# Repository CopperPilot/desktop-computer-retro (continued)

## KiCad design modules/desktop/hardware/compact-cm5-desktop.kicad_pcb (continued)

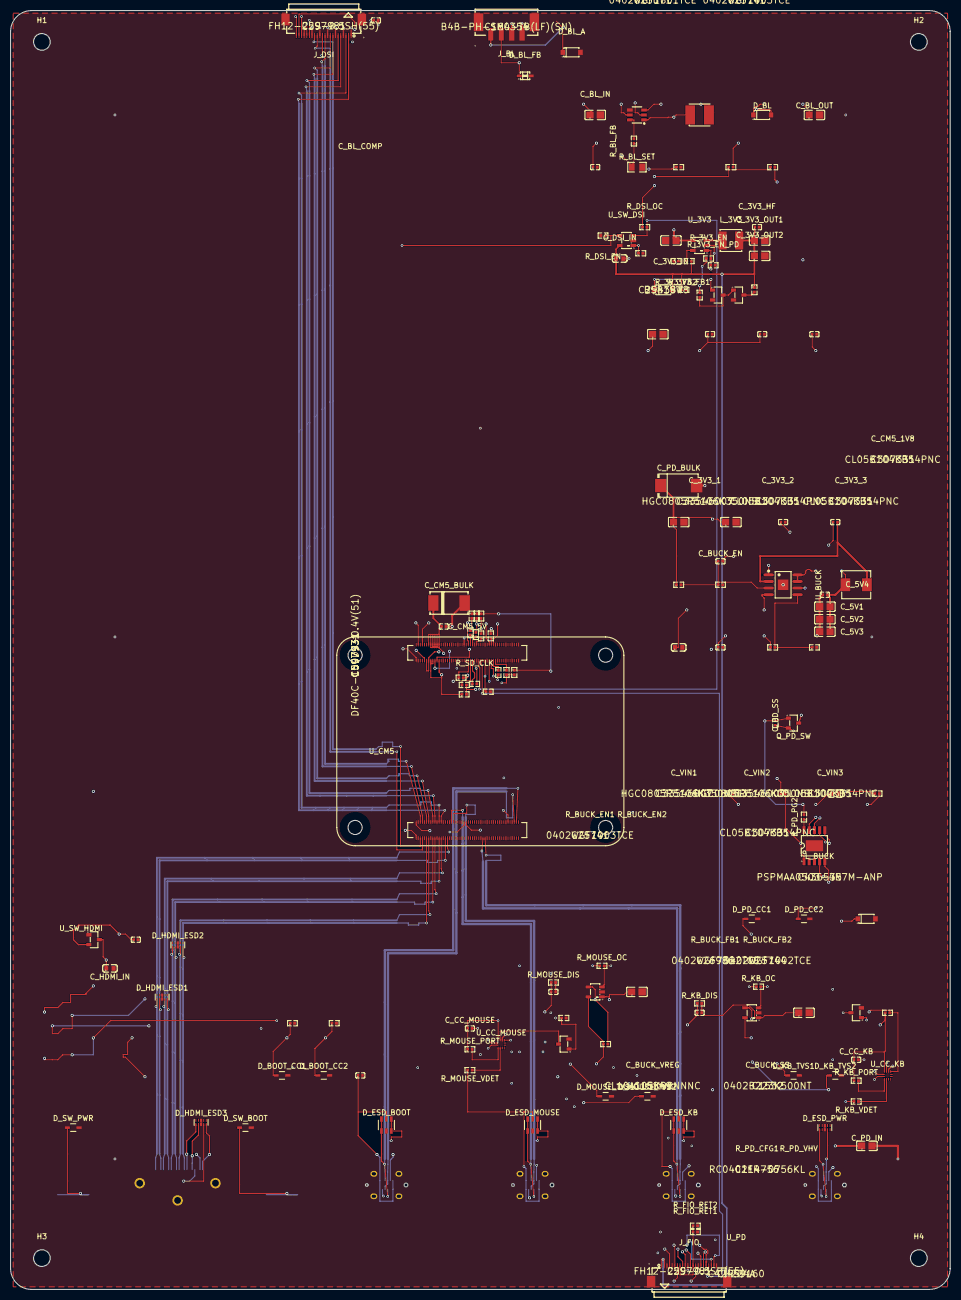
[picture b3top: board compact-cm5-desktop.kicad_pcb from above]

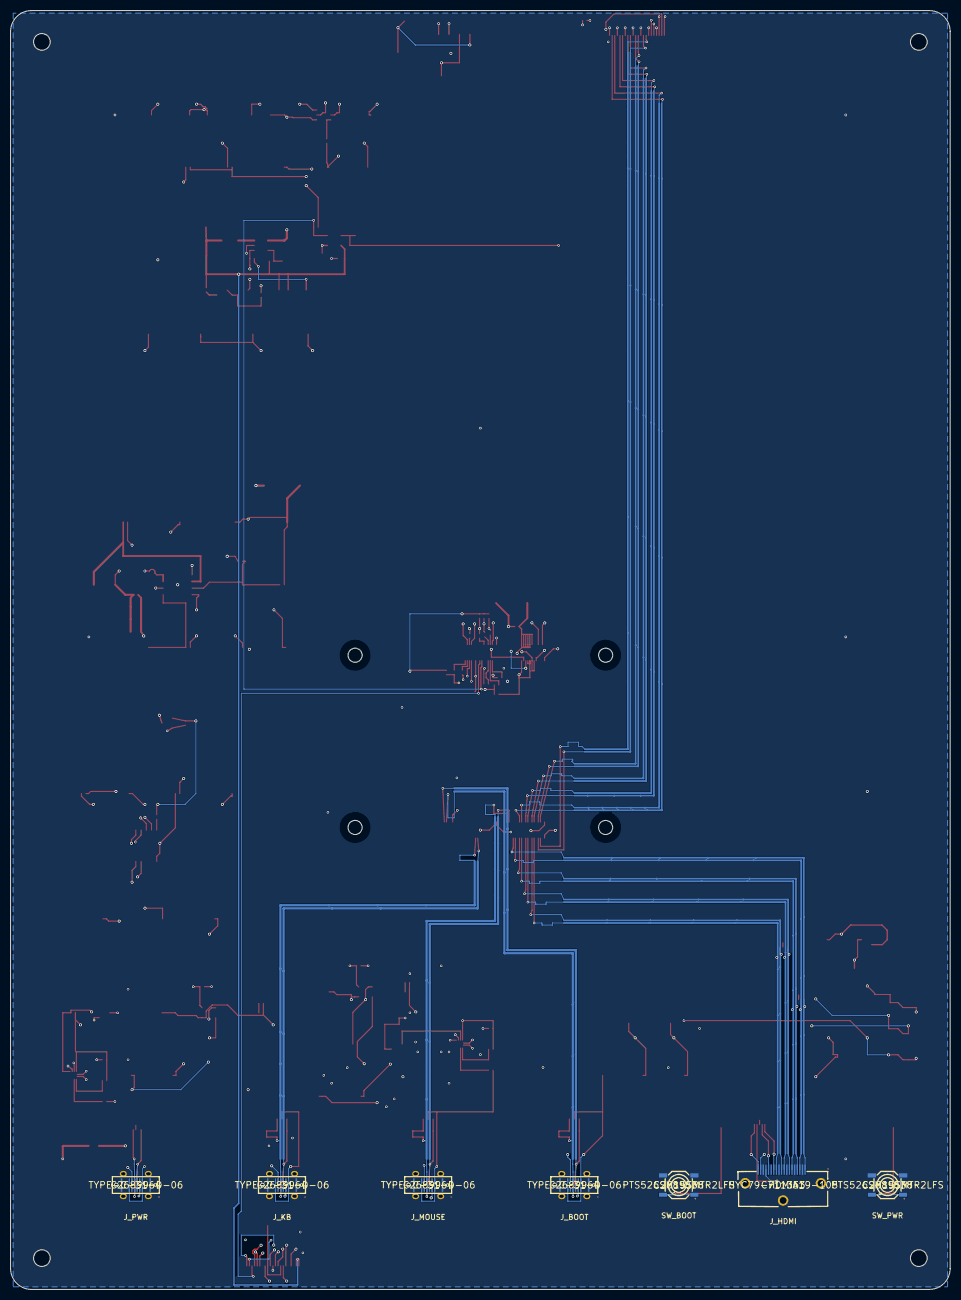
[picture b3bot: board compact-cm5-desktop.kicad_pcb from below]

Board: 4 copper layers, 180.0 x 245.0 mm, 147 parts (7 on the bottom side), 112 nets.

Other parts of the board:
H1, H2, H3, H4: MountingHole_3.2mm_M3

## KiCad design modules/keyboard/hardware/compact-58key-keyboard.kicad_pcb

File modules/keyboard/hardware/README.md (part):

# KiCad project — Compact 58-Key Mechanical Desktop Keyboard

Generated from `rea/spec.yaml` by rea-hardware (fab rules, stackup, outline at the origin, mounting
holes), then completed by the electrical agent. Every placed part carries an `LCSC` field and matches
the 150-component `rea/spec.yaml` BOM 1-for-1.

## Architecture & Programming / Bootloader Path

- **MCU & Clocking (`U1`, RP2040, LCSC `C2040`)**:
  - Powered by `3V3_KB` (`IOVDD`, `USB_VDD`, `ADC_AVDD`, `VREG_IN`) with the internal core regulator generating `+1V1` on `VREG_VOUT` (Pin 45) for `DVDD` (Pins 23, 50).
  - Clocked by a 12.000 MHz SMD3225-4P crystal (`Y1`, Abracon `ABM8-272-T3`, LCSC `C20625731`, rated `C_L = 10 pF`, `ESR <= 50 Ohm` max per RP2040 XOSC specification) matched to 12 pF load capacitors (`C15`, `C16`, LCSC `C1547`, giving `C_load = (12 pF * 12 pF) / 24 pF + 4 pF stray = 10 pF`) and a 1 kOhm damping resistor (`R5`, LCSC `C11702`) on `XOUT`.
  - **Crystal Placement & Layout (`Y1`, `R5`, `C15`, `C16`)**: Placed immediately south of `U1` Pins 20 (`XIN`) and 21 (`XOUT`) at `(186.60, 22.65)` mm (`C15` at `(184.10, 22.65)`, `R5` at `(189.30, 21.65)`, `C16` at `(189.30, 23.35)`). `/XIN`, `/XOUT_MCU`, and `/XOUT_XTAL` are routed 100% on `F.Cu` with zero vias over a continuous, unbroken `B.Cu` ground plane (`/COL9` and `/COL10` are routed outside the crystal boundary at `x <= 183.87 mm`).
- **QSPI Flash, UF2 USB Bootloader & Reset Path (`U2`, `R7`, `SW59`, `R6`, `R8`, `J1`)**:
  - External 16 MB QSPI NOR flash `U2` (`W25Q128JVSIQ`, LCSC `C97521`) connects to `U1` `QSPI_SS`, `QSPI_SCLK`, and `QSPI_SD0..SD3`.
  - A 10 kOhm 1% pull-up resistor `R7` (`0402WGF1002TCE`, LCSC `C25744`) placed adjacent to `U2.1` (`~{CS}`) pulls `QSPI_SS_N` up to `3V3_KB` so that flash `~{CS}` tracks `3V3_KB` during power-up and reset while `U1.56` is tri-stated.
  - Bottom-mounted tactile switch `SW59` (`TS-1187A-B-A-B`, LCSC `C318884`, aligned with the bottom enclosure aperture `F_BOOTSEL` and captive actuator `A_BOOTSEL`) pulls `QSPI_SS_N` to `GND` through a 1 kOhm isolation resistor (`R6`, LCSC `C11702`). When `SW59` is pressed, the `R6` / `R7` divider pulls `QSPI_SS_N` to `3.3 V * (1 kOhm / 11 kOhm) = 0.30 V` (`< 0.8 V` `V_IL,max` of `U1` and `U2`).
  - `U1.26` (`RUN`) is pulled up to `3V3_KB` via 10 kOhm 1% resistor `R8` (`0402WGF1002TCE`, LCSC `C25744` at `(196.30, 19.00)` mm).
  - **Reachable post-assembly flashing sequence**: Holding `SW59` via the underside `BOOTSEL` button while plugging the USB-C cable into rear receptacle `J1` (`P_KB_DEV`) powers `VBUS_RAW` -> `F1` (`5V_USB_KB`) -> `U3` (`3V3_KB`) -> `U1` (`VREG_VOUT` = `+1V1`), starts the 12 MHz crystal oscillator (`Y1`), and samples `QSPI_SS_N` low (`0.30 V`) at power-on reset. The RP2040 ROM bootloader then enumerates directly over the wired USB 2.0 D+/D- path (`J1` -> `U4` ESD protection -> `R3`/`R4` 27 Ohm series terminations -> `U1` Pins 46/47) as a USB Mass Storage UF2 programming device without requiring enclosure disassembly.

## Component Rating, Power Tree, ESD Protection & Thermal Verification

- **Coordinated Overcurrent & ESD Protection (`J1`, `C17`, `U4`, `F1`, `D60`, `R1`, `R2`)**:
  - `J1` (`TYPE-C-31-M-12`, LCSC `C165948`): dual `VBUS` contacts (`A4B9`, `B4A9` on `VBUS_RAW`) and dual `GND` contacts (`A1B12`, `B1A12`) plus 4 TH shield tabs rated **5.0 A** total (>= 1.25 A per power contact), exceeding the 0.5 A rail limit and ~65 mA active keyboard current with > 10x margin.
  - **High-Frequency Connector-Side ESD Decoupling & Data-Line Clamping (`C17`, `U4`)**:
    - Local 100 nF 16 V X7R high-frequency ESD decoupling capacitor `C17` (`CL05B104KO5NNNC`, LCSC `C1525` at `(156.40, 8.40)` mm) connects directly between `/VBUS_RAW` and `GND` at `J1` ahead of `F1`.
    - `U4` (`USBLC6-2SC6`, LCSC `C2827654`) is placed immediately adjacent to `J1` at `(159.50, 8.40)` mm (`<= 3 mm` from `J1` pads on `F.Cu` with in-line flow-through routing on `/USB_CONN_DP` and `/USB_CONN_DM`), with Pin 5 (`VBUS`) referenced to `/5V_USB_KB` downstream of `F1` so sustained overvoltage or reverse-polarity faults are current-limited by `F1`.
  - **Series PTC Fuse Isolation & Fuse-Coordinated Shunt TVS Clamping on `5V_USB_KB` (`F1`, `D60`, `C1`)**:
    - `F1` (`BSMD0805-050-24V`, LCSC `C910822`, 0805 PTC resettable fuse at `(158.50, 11.80)` mm): connected in series between `/VBUS_RAW` and `/5V_USB_KB`, rated **24 V**, **500 mA** hold current, **1.0 A** trip current, and **40 A** maximum fault current ($R_{\text{min}} = 0.15\,\Omega$, $R_{\text{typ}} = 0.35\,\Omega$, $R_{1\text{max}} = 0.85\,\Omega$).
    - Immediately downstream of `F1.2` on `/5V_USB_KB` sits a 400 W, 43.6 A peak-pulse, low-clamping 5.0 V unidirectional TVS diode `D60` (`PTVS5V0S1UR-FS`, LCSC `C5380694`, SOD-123FL at `(158.50, 13.90)` mm, $V_{\text{RWM}} = 5.0\text{ V}$, $V_{\text{BR}} = 6.4\text{--}7.0\text{ V}$, $V_{\text{CL}} \le 9.2\text{ V}$ at $I_{\text{PP}} = 43.6\text{ A}$) alongside `U4.5` and 2.2 uF 25 V X7R input decoupling capacitor `C1` (`CL21B225KAFNNNE`, LCSC `C19110` at `(161.30, 12.60)` mm), providing fuse-coordinated overvoltage, reverse-polarity, and ESD clamping ahead of 20 V abs-max LDO `U3`.
  - USB-C UFP (sink) configuration: `CC1` (`J1.A5`) and `CC2` (`J1.B5`) each have dedicated 5.1 kOhm 1% pull-down resistors (`R1` at `(161.50, 3.30)` mm and `R2` at `(153.25, 8.50)` mm, `0402WGF5101TCE`, LCSC `C25905`) connected directly to `GND` on `F.Cu` with zero vias and zero stubs.
- **LDO Voltage Rating, Headroom, Monotonic Placement & Thermal Margin (`U3`, `C1`, `C2`, `C3`, `C4`)**:
  - `U3` (`LDL1117S33R`, STMicroelectronics, LCSC `C435835`, SOT-223-4 at `(166.95, 12.30)` mm in the monotonic power-entry path between `J1`/`F1` and `U2`/`U1`): 3.3 V fixed low-dropout regulator rated **18 V** maximum operating input / **20 V** absolute maximum input (`> 2x` worst-case TVS clamping voltage), **1.2 A** output current capability, low quiescent current **`I_Q = 250 uA` typical / `500 uA` max** (`<< 2.5 mA` USB 2.0 suspend limit), and low dropout **`V_DO = 350 mV` typ / `600 mV` max at 1.2 A** (`< 150 mV` at 250 mA).
  - **Worst-Case Dropout Margin (`> 680 mV` headroom)**: At minimum USB 2.0 bus voltage `VBUS_RAW = 4.40 V`, `I_load = 0.25 A`, and post-trip `R_F1,1max = 0.85 Ohm`, `V_IN,min(U3) = 4.40 V - 0.25 A * 0.85 Ohm = 4.188 V >> 3.35 V + 0.15 V = 3.50 V`.
  - **SOT-223-4 Thermal Margin at Full 0.25 A Continuous Specification**: In SOT-223-4 ($R_{\theta\text{JA}} \approx 60^\circ\text{C/W}$), delivering the full `0.25 A` continuous `3V3_KB` specification in `prompt.md` at `V_IN = 5.0 V` dissipates $P_D = (5.0\text{ V} - 3.3\text{ V}) \times 0.25\text{ A} = 0.425\text{ W}$, producing a junction temperature rise of only $\Delta T_J \approx 25.5^\circ\text{C}$ ($T_J \approx 60.5^\circ\text{C} \ll 125^\circ\text{C}$ max at $35^\circ\text{C}$ enclosure ambient).
  - **Zero-Via Core Regulator & IOVDD Decoupling (`C3`, `C4`)**: `C3` (`1 uF` 25 V X5R, LCSC `C52923` at `(188.35, 10.20)` mm) connects directly on `F.Cu` (`w = 0.20-0.30 mm`, length `1.8 mm`, **zero vias**) to `U1` Pin 45 (`VREG_VOUT`, `/+1V1`), and `C4` (`1 uF` 25 V X5R, LCSC `C52923` at `(190.30, 12.30)` mm) connects directly on `F.Cu` (**zero vias**) to `U1` Pins 42, 43, and 44 (`VREG_IN`, `/3V3_KB`).
- **Capacitor Voltage Ratings (>= 1.5x maximum rail voltage) & USB 2.0 Hot-Plug Inrush Compliance**:
  - `VBUS_RAW` / `5V_USB_KB` rails (5.0 V nominal, 5.25 V max; 1.5x requirement = 7.88 V): `C1` (2.2 uF, **25 V**), `C17` (100 nF, **16 V**). Direct unswitched capacitance on `VBUS` is `2.3 uF <= 10 uF` (`11.5 uC <= 50 uC` USB 2.0 hot-plug limit).
  - `3V3_KB` rail (3.3 V nominal; 1.5x requirement = 4.95 V): `C2` (4.7 uF, **25 V**), `C4` (1 uF, **25 V**), `C7..C14` (8x 100 nF, **16 V**).
  - `+1V1` core rail (1.1 V nominal; 1.5x requirement = 1.65 V): `C3` (1 uF, **25 V**), `C5..C6` (2x 100 nF, **16 V**).
  - `12 MHz Crystal` load network (`XIN` / `XOUT_XTAL`, <= 3.3 V): `C15`, `C16` (12 pF C0G, **50 V**).
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
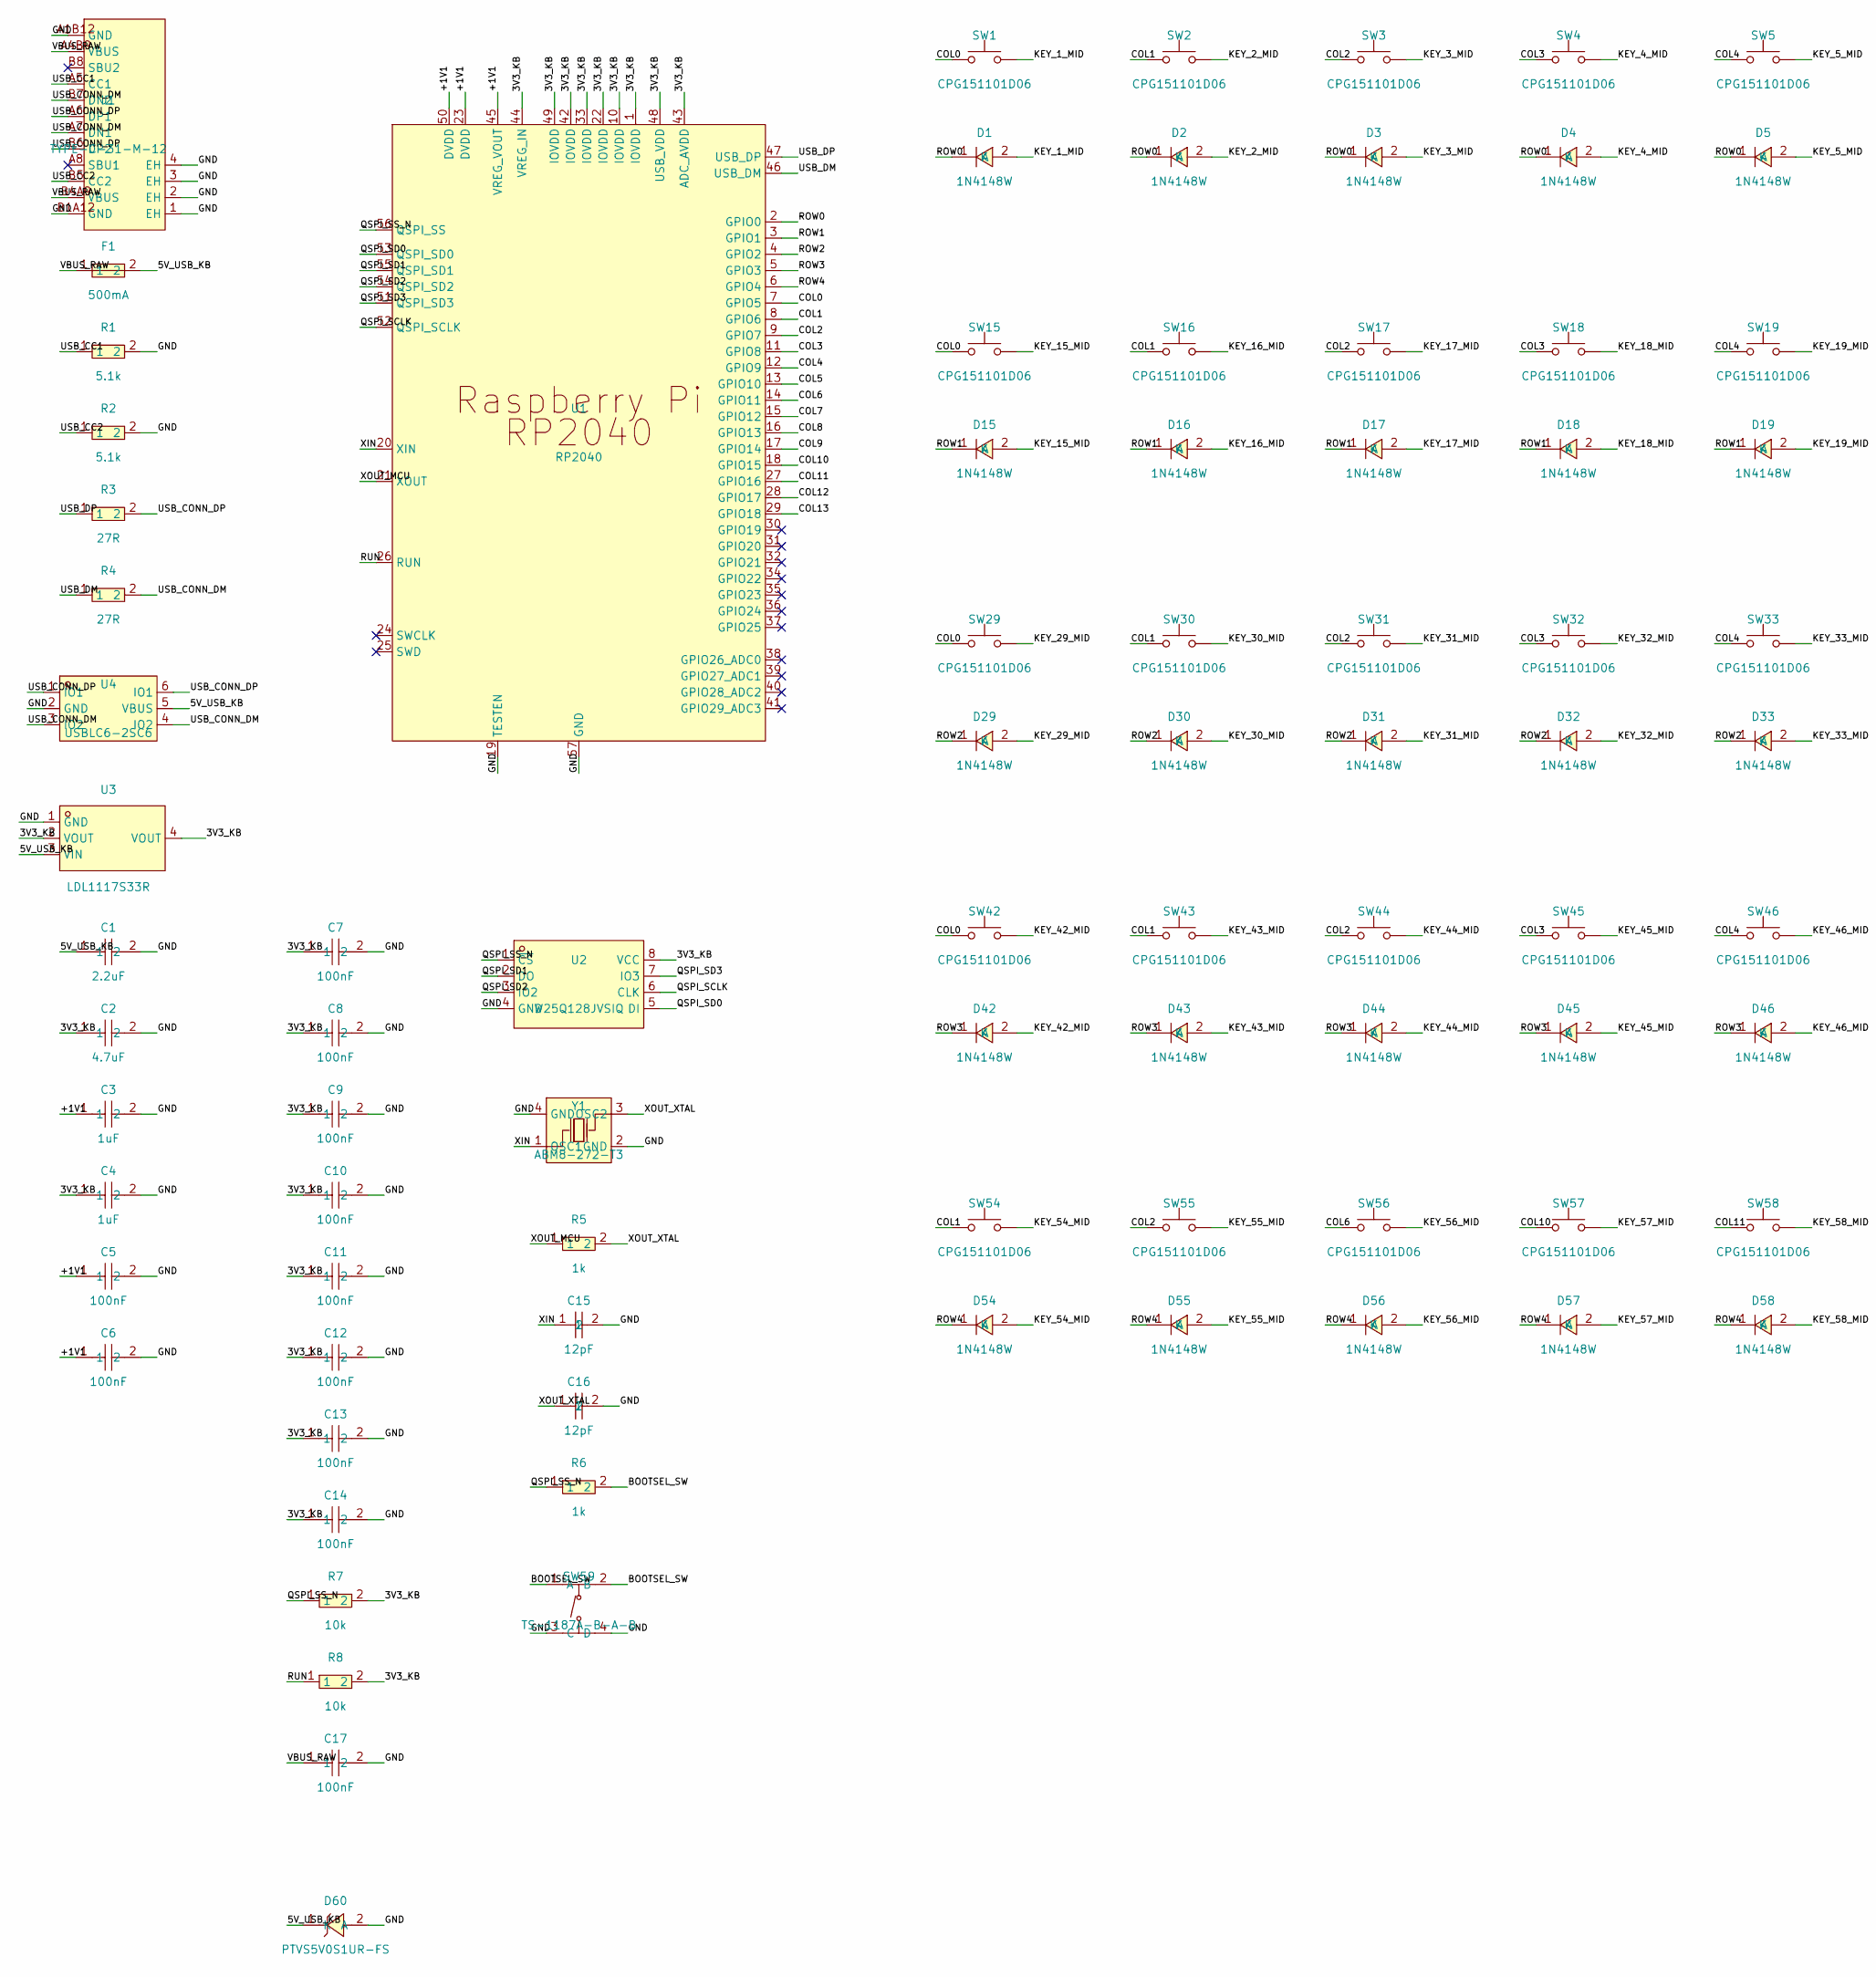
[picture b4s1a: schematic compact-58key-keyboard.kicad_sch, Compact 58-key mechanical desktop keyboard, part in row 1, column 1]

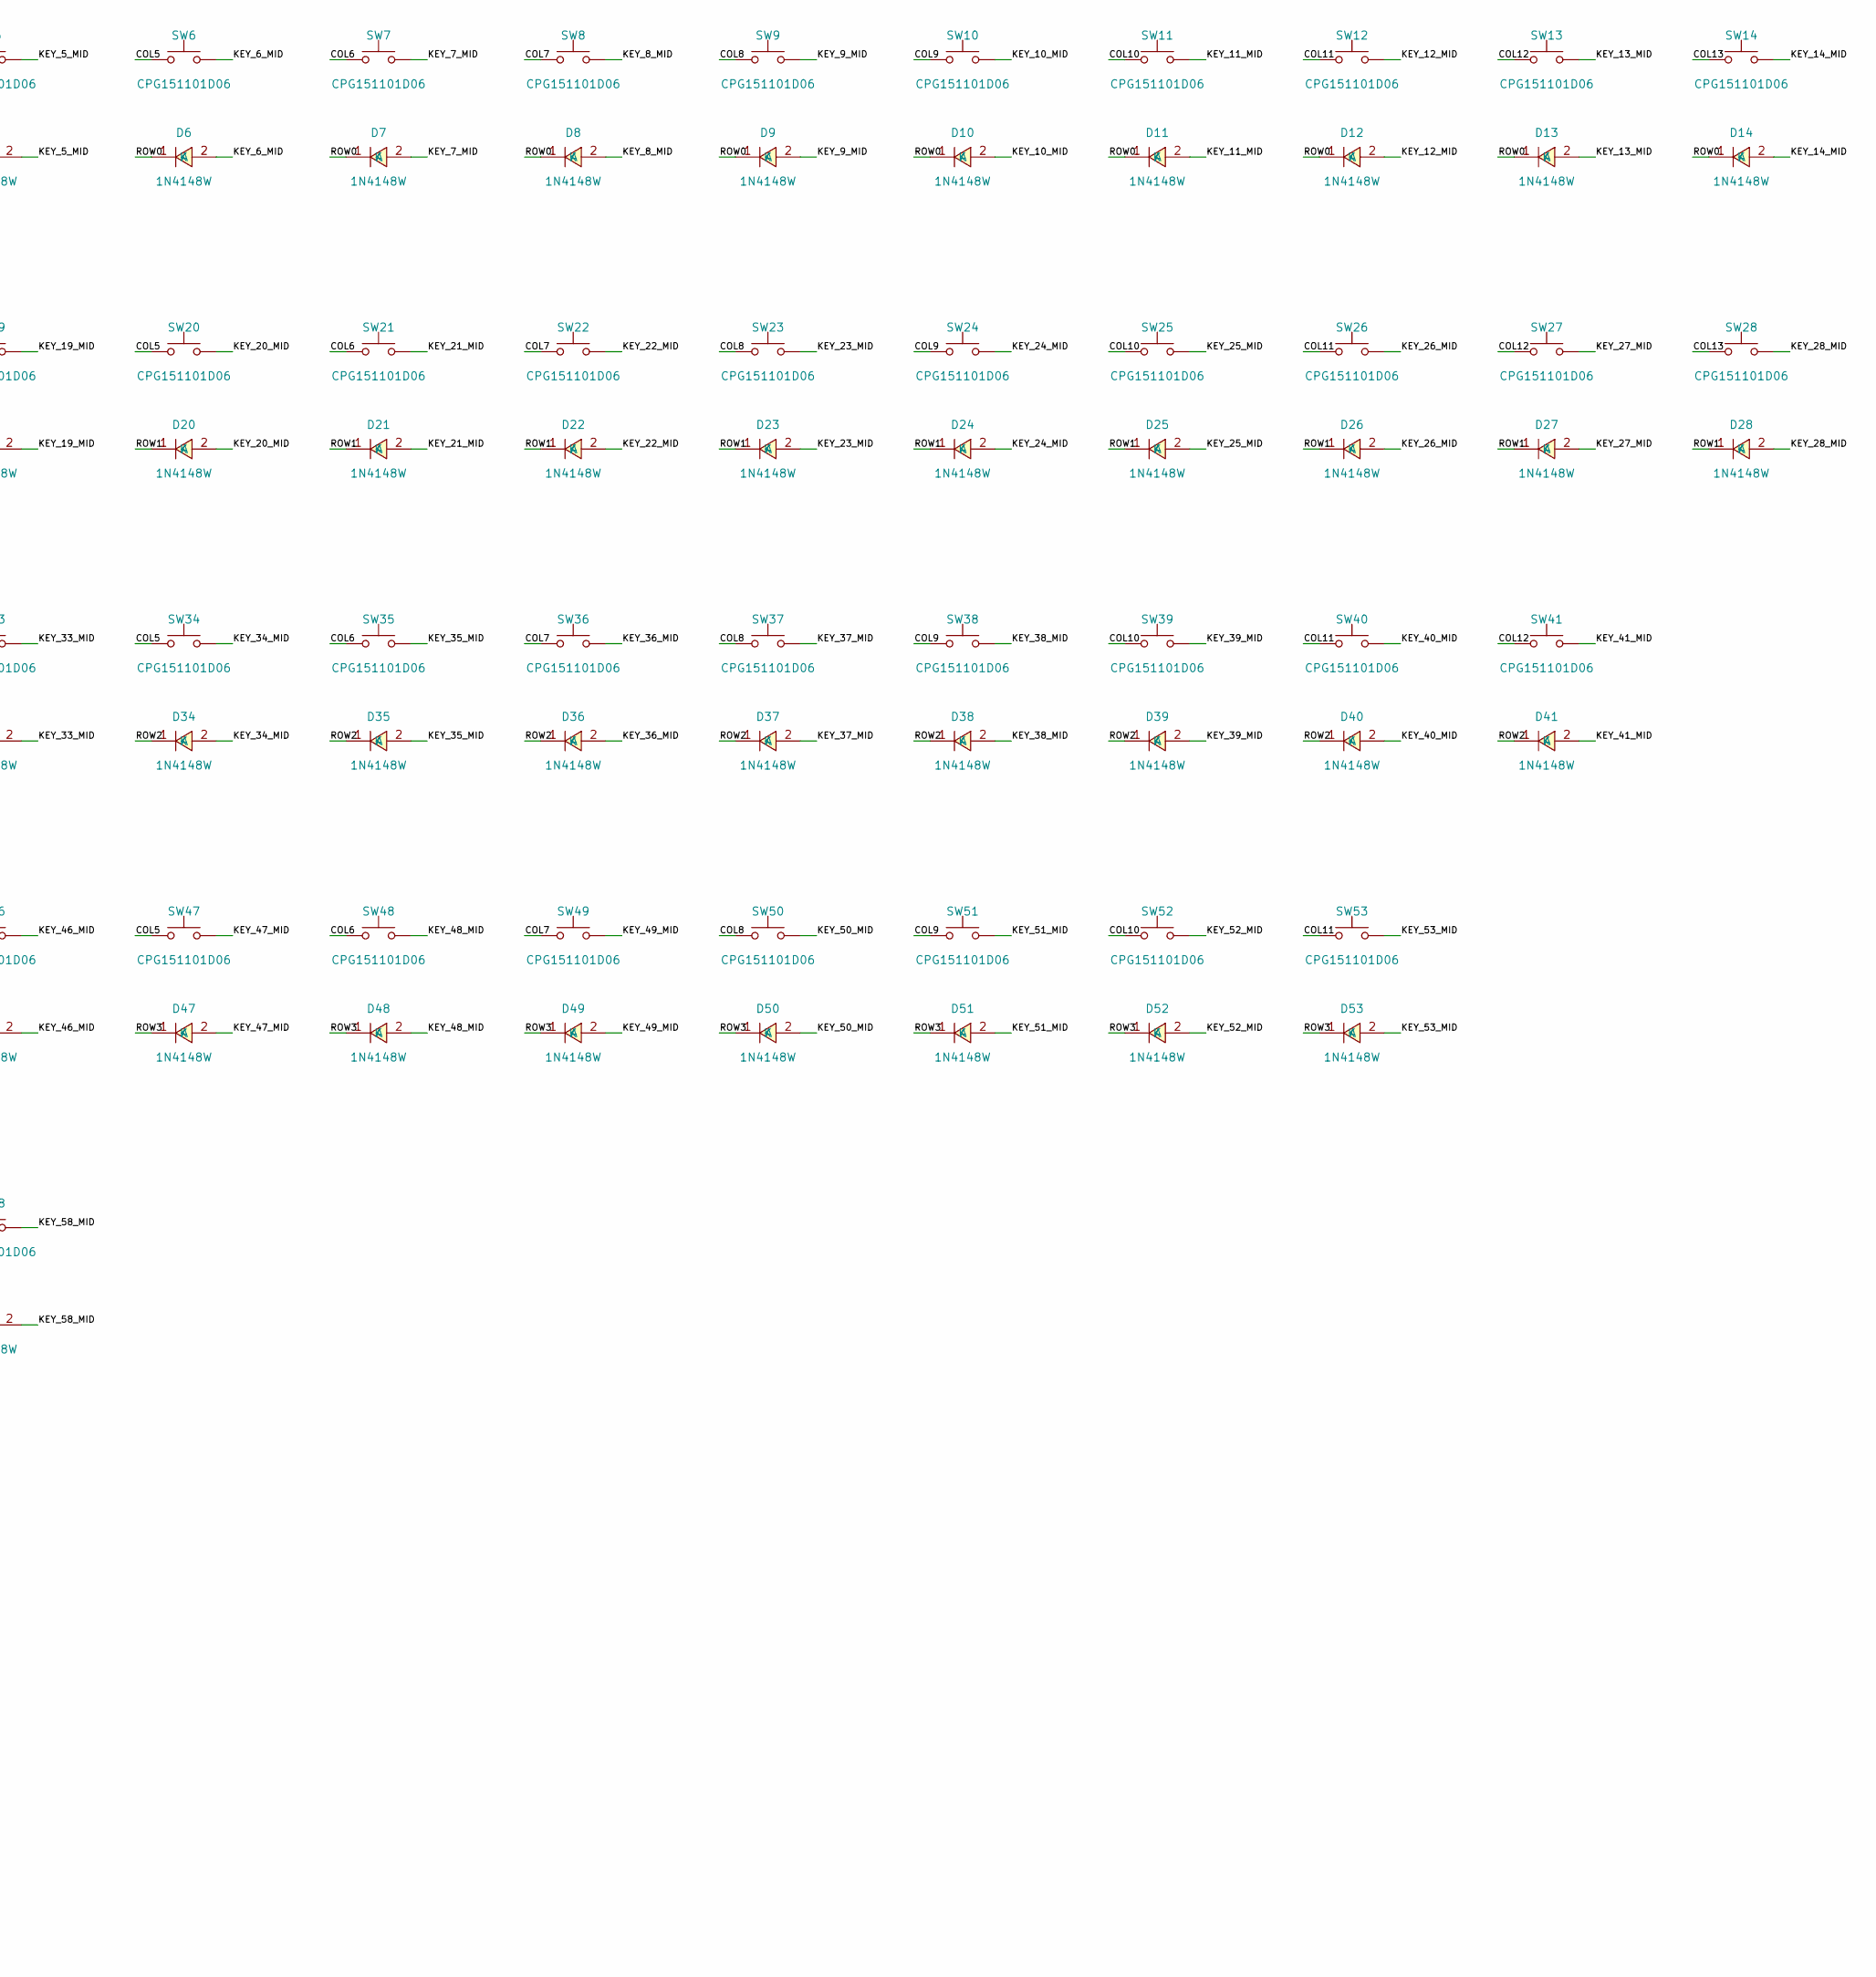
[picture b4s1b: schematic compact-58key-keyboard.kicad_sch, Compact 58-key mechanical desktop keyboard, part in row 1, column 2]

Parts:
C1: 2.2uF; C0805; MPN CL21B225KAFNNNE; LCSC C19110
C2: 4.7uF; C0805; MPN CL21A475KAQNNNE; LCSC C1779
C3, C4: 1uF; C0402; LCSC C52923
C5, C6, C7, C8, C9, C10, C11, C12, C13, C14, C17: 100nF; C0402; LCSC C1525
C15, C16: 12pF; C0402; LCSC C1547
D1, D2, D3, D4, D5, D6, D7, D8, D9, D10, D11, D12, D13, D14, D15, D16, D17, D18, D19, D20, D21, D22, D23, D24, D25, D26, D27, D28, D29, D30, D31, D32, D33, D34, D35, D36, D37, D38, D39, D40, D41, D42, D43, D44, D45, D46, D47, D48, D49, D50, D51, D52, D53, D54, D55, D56, D57, D58: 1N4148W; SOD-123F_L2.7-W1.6-LS3.8-RD; LCSC C81598
D60: PTVS5V0S1UR-FS; SOD-123FL_L2.7-W1.8-LS3.8-RD; MPN PTVS5V0S1UR-FS; LCSC C5380694
F1: 500mA; F0805; MPN BSMD0805-050-24V; LCSC C910822
J1: TYPE-C-31-M-12; USB-C_SMD-TYPE-C-31-M-12_1; LCSC C165948
R1, R2: 5.1k; R0402; LCSC C25905
R3, R4: 27R; R0402; LCSC C25156
R5, R6: 1k; R0402; LCSC C11702
R7, R8: 10k; R0402; MPN 0402WGF1002TCE; LCSC C25744
SW1, SW2, SW3, SW4, SW5, SW6, SW7, SW8, SW9, SW10, SW11, SW12, SW13, SW16, SW17, SW18, SW19, SW20, SW21, SW22, SW23, SW24, SW25, SW26, SW27, SW30, SW31, SW32, SW33, SW34, SW35, SW36, SW37, SW38, SW39, SW40, SW43, SW44, SW45, SW46, SW47, SW48, SW49, SW50, SW51, SW52: CPG151101D06; SW_Cherry_MX_1.00u_PCB; LCSC C49234237
SW14: CPG151101D06; SW_Cherry_MX_2.00u_PCB; LCSC C49234237
SW15, SW28, SW55, SW57: CPG151101D06; SW_Cherry_MX_1.50u_PCB; LCSC C49234237
SW29: CPG151101D06; SW_Cherry_MX_1.75u_PCB; LCSC C49234237
SW41, SW42: CPG151101D06; SW_Cherry_MX_2.25u_PCB; LCSC C49234237
SW53: CPG151101D06; SW_Cherry_MX_2.75u_PCB; LCSC C49234237
SW54, SW58: CPG151101D06; SW_Cherry_MX_1.25u_PCB; LCSC C49234237
SW56: CPG151101D06; SW_Cherry_MX_6.25u_PCB; LCSC C49234237
SW59: TS-1187A-B-A-B; SW-SMD_4P-L5.1-W5.1-P3.70-LS6.5-TL_H1.5; LCSC C318884
U1: RP2040; LQFN-56_L7.0-W7.0-P0.4-EP; LCSC C2040
U2: W25Q128JVSIQ; SOIC-8_L5.3-W5.3-P1.27-LS8.0-BL; LCSC C97521
U3: LDL1117S33R; SOT-223-4_L6.5-W3.5-P2.30-LS7.0-BR; MPN LDL1117S33R; LCSC C435835
U4: USBLC6-2SC6; SOT-23-6_L2.9-W1.6-P0.95-LS2.8-BL; LCSC C2827654
Y1: ABM8-272-T3; CRYSTAL-SMD_4P-L3.2-W2.5-BL; MPN ABM8-272-T3; LCSC C20625731

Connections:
/3V3_KB: C2.1, C4.1, C7.1, C8.1, C9.1, C10.1, C11.1, C12.1, C13.1, C14.1, R7.2, R8.2, U1.1 (IOVDD), U1.10 (IOVDD), U1.22 (IOVDD), U1.33 (IOVDD), U1.42 (IOVDD), U1.43 (ADC_AVDD), U1.44 (VREG_IN), U1.48 (USB_VDD), U1.49 (IOVDD), U2.8 (VCC), U3.2 (VOUT), U3.4 (VOUT)
/5V_USB_KB: C1.1, D60.1 (K), F1.2, U3.3 (VIN), U4.5 (VBUS)
/+1V1: C3.1, C5.1, C6.1, U1.23 (DVDD), U1.45 (VREG_VOUT), U1.50 (DVDD)
/BOOTSEL_SW: R6.2, SW59.1 (A), SW59.2 (B)
/COL0: SW1.1, SW15.1, SW29.1, SW42.1, U1.7 (GPIO5)
/COL1: SW2.1, SW16.1, SW30.1, SW43.1, SW54.1, U1.8 (GPIO6)
/COL2: SW3.1, SW17.1, SW31.1, SW44.1, SW55.1, U1.9 (GPIO7)
/COL3: SW4.1, SW18.1, SW32.1, SW45.1, U1.11 (GPIO8)
/COL4: SW5.1, SW19.1, SW33.1, SW46.1, U1.12 (GPIO9)
/COL5: SW6.1, SW20.1, SW34.1, SW47.1, U1.13 (GPIO10)
/COL6: SW7.1, SW21.1, SW35.1, SW48.1, SW56.1, U1.14 (GPIO11)
/COL7: SW8.1, SW22.1, SW36.1, SW49.1, U1.15 (GPIO12)
/COL8: SW9.1, SW23.1, SW37.1, SW50.1, U1.16 (GPIO13)
/COL9: SW10.1, SW24.1, SW38.1, SW51.1, U1.17 (GPIO14)
/COL10: SW11.1, SW25.1, SW39.1, SW52.1, SW57.1, U1.18 (GPIO15)
/COL11: SW12.1, SW26.1, SW40.1, SW53.1, SW58.1, U1.27 (GPIO16)
/COL12: SW13.1, SW27.1, SW41.1, U1.28 (GPIO17)
/COL13: SW14.1, SW28.1, U1.29 (GPIO18)
/GND: C1.2, C2.2, C3.2, C4.2, C5.2, C6.2, C7.2, C8.2, C9.2, C10.2, C11.2, C12.2, C13.2, C14.2, C15.2, C16.2, C17.2, D60.2 (A), J1.1 (EH), J1.2 (EH), J1.3 (EH), J1.4 (EH), J1.A1B12 (GND), J1.B1A12 (GND), R1.2, R2.2, SW59.3 (C), SW59.4 (D), U1.19 (TESTEN), U1.57 (GND), U2.4 (GND), U3.1 (GND), U4.2 (GND), Y1.2 (GND), Y1.4 (GND)
/KEY_1_MID: D1.2 (A), SW1.2
/KEY_2_MID: D2.2 (A), SW2.2
/KEY_3_MID: D3.2 (A), SW3.2
/KEY_4_MID: D4.2 (A), SW4.2
/KEY_5_MID: D5.2 (A), SW5.2
/KEY_6_MID: D6.2 (A), SW6.2
/KEY_7_MID: D7.2 (A), SW7.2
/KEY_8_MID: D8.2 (A), SW8.2
/KEY_9_MID: D9.2 (A), SW9.2
/KEY_10_MID: D10.2 (A), SW10.2
/KEY_11_MID: D11.2 (A), SW11.2
/KEY_12_MID: D12.2 (A), SW12.2
/KEY_13_MID: D13.2 (A), SW13.2
/KEY_14_MID: D14.2 (A), SW14.2
/KEY_15_MID: D15.2 (A), SW15.2
/KEY_16_MID: D16.2 (A), SW16.2
/KEY_17_MID: D17.2 (A), SW17.2
/KEY_18_MID: D18.2 (A), SW18.2
/KEY_19_MID: D19.2 (A), SW19.2
/KEY_20_MID: D20.2 (A), SW20.2
/KEY_21_MID: D21.2 (A), SW21.2
/KEY_22_MID: D22.2 (A), SW22.2
/KEY_23_MID: D23.2 (A), SW23.2
/KEY_24_MID: D24.2 (A), SW24.2
/KEY_25_MID: D25.2 (A), SW25.2
/KEY_26_MID: D26.2 (A), SW26.2
/KEY_27_MID: D27.2 (A), SW27.2
/KEY_28_MID: D28.2 (A), SW28.2
/KEY_29_MID: D29.2 (A), SW29.2
/KEY_30_MID: D30.2 (A), SW30.2
/KEY_31_MID: D31.2 (A), SW31.2
/KEY_32_MID: D32.2 (A), SW32.2
/KEY_33_MID: D33.2 (A), SW33.2
/KEY_34_MID: D34.2 (A), SW34.2
/KEY_35_MID: D35.2 (A), SW35.2
/KEY_36_MID: D36.2 (A), SW36.2
/KEY_37_MID: D37.2 (A), SW37.2
/KEY_38_MID: D38.2 (A), SW38.2
/KEY_39_MID: D39.2 (A), SW39.2
/KEY_40_MID: D40.2 (A), SW40.2
/KEY_41_MID: D41.2 (A), SW41.2
/KEY_42_MID: D42.2 (A), SW42.2
/KEY_43_MID: D43.2 (A), SW43.2
/KEY_44_MID: D44.2 (A), SW44.2
/KEY_45_MID: D45.2 (A), SW45.2
/KEY_46_MID: D46.2 (A), SW46.2
/KEY_47_MID: D47.2 (A), SW47.2
/KEY_48_MID: D48.2 (A), SW48.2
/KEY_49_MID: D49.2 (A), SW49.2
/KEY_50_MID: D50.2 (A), SW50.2
/KEY_51_MID: D51.2 (A), SW51.2
/KEY_52_MID: D52.2 (A), SW52.2
/KEY_53_MID: D53.2 (A), SW53.2
/KEY_54_MID: D54.2 (A), SW54.2
/KEY_55_MID: D55.2 (A), SW55.2
/KEY_56_MID: D56.2 (A), SW56.2
/KEY_57_MID: D57.2 (A), SW57.2
/KEY_58_MID: D58.2 (A), SW58.2
/QSPI_SCLK: U1.52 (QSPI_SCLK), U2.6 (CLK)
/QSPI_SD0: U1.53 (QSPI_SD0), U2.5 (DI)
/QSPI_SD1: U1.55 (QSPI_SD1), U2.2 (DO)
/QSPI_SD2: U1.54 (QSPI_SD2), U2.3 (IO2)
/QSPI_SD3: U1.51 (QSPI_SD3), U2.7 (IO3)
/QSPI_SS_N: R6.1, R7.1, U1.56 (QSPI_SS), U2.1 (~CS)
/ROW0: D1.1 (K), D2.1 (K), D3.1 (K), D4.1 (K), D5.1 (K), D6.1 (K), D7.1 (K), D8.1 (K), D9.1 (K), D10.1 (K), D11.1 (K), D12.1 (K), D13.1 (K), D14.1 (K), U1.2 (GPIO0)
/ROW1: D15.1 (K), D16.1 (K), D17.1 (K), D18.1 (K), D19.1 (K), D20.1 (K), D21.1 (K), D22.1 (K), D23.1 (K), D24.1 (K), D25.1 (K), D26.1 (K), D27.1 (K), D28.1 (K), U1.3 (GPIO1)
/ROW2: D29.1 (K), D30.1 (K), D31.1 (K), D32.1 (K), D33.1 (K), D34.1 (K), D35.1 (K), D36.1 (K), D37.1 (K), D38.1 (K), D39.1 (K), D40.1 (K), D41.1 (K), U1.4 (GPIO2)
/ROW3: D42.1 (K), D43.1 (K), D44.1 (K), D45.1 (K), D46.1 (K), D47.1 (K), D48.1 (K), D49.1 (K), D50.1 (K), D51.1 (K), D52.1 (K), D53.1 (K), U1.5 (GPIO3)
/ROW4: D54.1 (K), D55.1 (K), D56.1 (K), D57.1 (K), D58.1 (K), U1.6 (GPIO4)
/RUN: R8.1, U1.26 (RUN)
/USB_CC1: J1.A5 (CC1), R1.1
/USB_CC2: J1.B5 (CC2), R2.1
/USB_CONN_DM: J1.A7 (DN1), J1.B7 (DN2), R4.2, U4.3 (IO2), U4.4 (IO2)
/USB_CONN_DP: J1.A6 (DP1), J1.B6 (DP2), R3.2, U4.1 (IO1), U4.6 (IO1)
/USB_DM: R4.1, U1.46 (USB_DM)
/USB_DP: R3.1, U1.47 (USB_DP)
/VBUS_RAW: C17.1, F1.1, J1.A4B9 (VBUS), J1.B4A9 (VBUS)
/XIN: C15.1, U1.20 (XIN), Y1.1 (OSC1)
/XOUT_MCU: R5.1, U1.21 (XOUT)
/XOUT_XTAL: C16.1, R5.2, Y1.3 (OSC2)

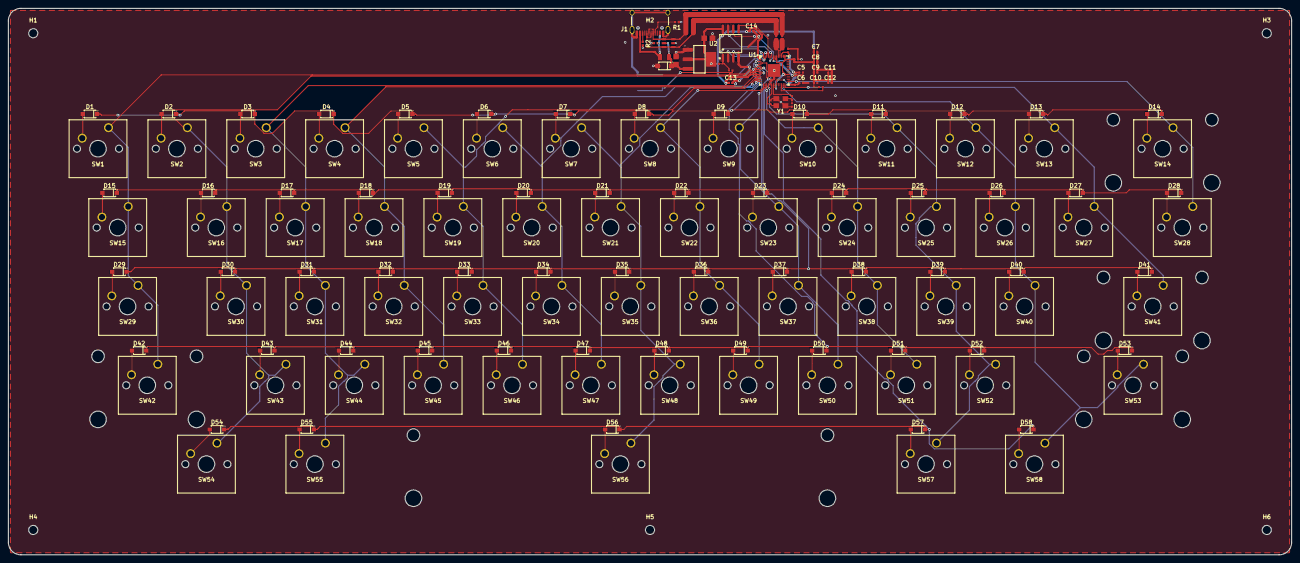
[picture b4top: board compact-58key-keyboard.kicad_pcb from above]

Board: 2 copper layers, 310.0 x 132.0 mm, 156 parts (1 on the bottom side), 99 nets.

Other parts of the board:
H1, H2, H3, H4, H5, H6: MountingHole_2.2mm_M2

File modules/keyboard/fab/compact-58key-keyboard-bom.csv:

Comment,Designator,Footprint,LCSC Part #
2.2uF,C1,C0805,C19110
100nF,"C5,C6,C7,C8,C9,C10,C11,C12,C13,C14,C17",C0402,C1525
12pF,"C15,C16",C0402,C1547
4.7uF,C2,C0805,C1779
1uF,"C3,C4",C0402,C52923
1N4148W,"D1,D2,D3,D4,D5,D6,D7,D8,D9,D10,D11,D12,D13,D14,D15,D16,D17,D18,D19,D20,D21,D22,D23,D24,D25,D26,D27,D28,D29,D30,D31,D32,D33,D34,D35,D36,D37,D38,D39,D40,D41,D42,D43,D44,D45,D46,D47,D48,D49,D50,D51,D52,D53,D54,D55,D56,D57,D58",SOD-123F_L2.7-W1.6-LS3.8-RD,C81598
PTVS5V0S1UR-FS,D60,SOD-123FL_L2.7-W1.8-LS3.8-RD,C5380694
500mA,F1,F0805,C910822
TYPE-C-31-M-12,J1,USB-C_SMD-TYPE-C-31-M-12_1,C165948
5.1k,"R1,R2",R0402,C25905
27R,"R3,R4",R0402,C25156
1k,"R5,R6",R0402,C11702
10k,"R7,R8",R0402,C25744
CPG151101D06,"SW1,SW2,SW3,SW4,SW5,SW6,SW7,SW8,SW9,SW10,SW11,SW12,SW13,SW16,SW17,SW18,SW19,SW20,SW21,SW22,SW23,SW24,SW25,SW26,SW27,SW30,SW31,SW32,SW33,SW34,SW35,SW36,SW37,SW38,SW39,SW40,SW43,SW44,SW45,SW46,SW47,SW48,SW49,SW50,SW51,SW52",SW_Cherry_MX_1.00u_PCB,C49234237
CPG151101D06,SW14,SW_Cherry_MX_2.00u_PCB,C49234237
CPG151101D06,"SW15,SW28,SW55,SW57",SW_Cherry_MX_1.50u_PCB,C49234237
CPG151101D06,SW29,SW_Cherry_MX_1.75u_PCB,C49234237
CPG151101D06,"SW41,SW42",SW_Cherry_MX_2.25u_PCB,C49234237
CPG151101D06,SW53,SW_Cherry_MX_2.75u_PCB,C49234237
CPG151101D06,"SW54,SW58",SW_Cherry_MX_1.25u_PCB,C49234237
CPG151101D06,SW56,SW_Cherry_MX_6.25u_PCB,C49234237
TS-1187A-B-A-B,SW59,SW-SMD_4P-L5.1-W5.1-P3.70-LS6.5-TL_H1.5,C318884
RP2040,U1,LQFN-56_L7.0-W7.0-P0.4-EP,C2040
W25Q128JVSIQ,U2,SOIC-8_L5.3-W5.3-P1.27-LS8.0-BL,C97521
LDL1117S33R,U3,SOT-223-4_L6.5-W3.5-P2.30-LS7.0-BR,C435835
USBLC6-2SC6,U4,SOT-23-6_L2.9-W1.6-P0.95-LS2.8-BL,C2827654
ABM8-272-T3,Y1,CRYSTAL-SMD_4P-L3.2-W2.5-BL,C20625731

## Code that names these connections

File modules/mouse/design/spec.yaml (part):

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    - id: mcu_hid
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      key_parts: [STM32F042K6T6, PTS526SM15SMTR2LFS, PESD3V3L1BA, RH-5015]
      reference: "ST AN2606 STM32 System Memory Boot Mode (USB DFU on PA11/PA12 with BOOT0 active-high)"
    - id: optical_sensor
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      key_parts: [PMW3901MB-TXQT, KT-0603R, AO3400A]
      reference: "PixArt PMW3901MB-TXQT Optical Motion Tracking Sensor Datasheet Application Circuit"
  nets_must_connect:
    - ["J1.A6", "U1.PA12"]
    - ["J1.B6", "U1.PA12"]
    - ["J1.A7", "U1.PA11"]
    - ["J1.B7", "U1.PA11"]
    - ["U2.SCLK", "U1.PA5"]
    - ["U2.MISO", "U1.PA6"]
    - ["U2.MOSI", "U1.PA7"]
    - ["U2.NCS", "U1.PA4"]
    - ["U2.MOTION", "U1.PB0"]
    - ["U2.NRESET", "U1.PB1"]
    - ["U1.PA1", "Q1.G"]
  high_speed:
    - name: USB2_DEV
      kind: diff_pairs
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    mpn: AO3400A
    lcsc: C20917
    footprint: "lcsc:SOT-23-3_L2.9-W1.3-P1.90-LS2.4-BR"
    description: "30V 5.7A N-channel enhancement MOSFET (R_DS(on) <= 48 mOhm @ V_GS = 2.5V) switching D2/D3 cathode return net OPT_LED_K to GND under U1.PA1 (OPT_LED_EN) control for USB 2.0 suspend compliance"
  - refs: [Q2]
    role: vbus_rpp_pmos
    mpn: AO3401A
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    mpn: USBLC6-2SC6
    lcsc: C2687116
    footprint: "lcsc:SOT-23-6_L2.9-W1.6-P0.95-LS2.8-BL"
    description: "USB 2.0 D+/D- low-capacitance 8/20 us IEC 61000-4-2 transient ESD protection array with pin 5 (VBUS reference) and C11 (1 uF 50V) connected on VBUS_PROT downstream of F1 and reverse-polarity P-MOSFET Q2 (used strictly for transient ESD clamping, never as a DC crowbar)"
  - refs: [D6]
    role: vbus_gate_zener
    mpn: BZT52C8V2S
    lcsc: C22375294
    footprint: "lcsc:SOD-323_L1.7-W1.3-LS2.6-RD-1"
    description: "8.2V (7.7-8.7V) 200mW SOD-323 Zener diode between Q2 Source (VBUS_PROT, Cathode) and Q2 Gate (VBUS_Q2_G, Anode) clamping |V_GS| <= 8.7V < 12V abs max on high-voltage transients (I_R <= 700 nA @ 5V)"
  - refs: [D2, D3]
    role: illumination_led
    mpn: KT-0603R
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    mpn: CL10A475KO8NNNC
    lcsc: C19666
    footprint: "lcsc:C0603"
    description: "4.7uF 16V X5R 0603 decoupling capacitors on 2V0_SENSOR (C3) and PMW3901MB-TXQT internal regulator pin SENSOR_VREG (C4)"
  - refs: [C5, C6, C7, C8, C9, C10, C12, C14]
    role: decoupling_cap
    mpn: CC0603KRX7R9BB104
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  - question: "MCU and firmware flashing mechanism?"
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    reason: "STM32F042K6T6 includes crystal-less USB 2.0 FS with HSI48 + Clock Recovery System (CRS) and native ROM USB DFU bootloader on PA11/PA12 when BOOT0 is latched high on the 4th rising edge of SYSCLK after POR (held stable across contact bounce by C14 = 100 nF with R3 = 10k and R8 = 1k)."

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
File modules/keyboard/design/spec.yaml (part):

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    purpose: Rear-edge USB-C 2.0 receptacle (J1, port P_KB_DEV), 5.1 kOhm CC1/CC2 UFP pull-down resistors
      (R1, R2), local 100 nF high-frequency ESD decoupling capacitor (C17) on VBUS_RAW at J1 ahead of
      F1, USBLC6-2SC6 ESD protection (U4) placed immediately adjacent to J1 with in-line flow-through
      routing on USB_CONN_DP/USB_CONN_DM and pin 5 (VBUS) referenced to 5V_USB_KB behind F1, 500 mA PTC
      resettable fuse (F1, BSMD0805-050-24V), fuse-coordinated PTVS5V0S1UR-FS 5.0 V unidirectional TVS
      diode (D60, V_CL <= 9.2 V at 43.6 A) and 2.2 uF LDO input decoupling (C1) on 5V_USB_KB downstream
      of F1, and 18 V operating / 20 V abs-max, low-IQ (250 uA typ), low-dropout (350 mV typ at 1.2 A)
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      Reference Design)
  - id: key_matrix
    purpose: 5-row by 14-column full anti-ghosting diode keymatrix wiring all 58 Cherry MX keyswitches
      (SW1..SW58) and 58 1N4148W SOD-123 diodes (D1..D58) to 19 RP2040 GPIOs (ROW0..ROW4 on GPIO0..GPIO4,
      COL0..COL13 on GPIO5..GPIO18)
    key_parts:
    - CPG151101D06 (C49234237)
    - 1N4148W (C81598)
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    file: case/out/bottom_shell.stl
    role: shell
    process: mjf
    material: PA12
    finish: matte warm-grey / beige
    color: '#d8d0c0'
    description: 'Stepped wedge lower chassis pan (X: -14..324, Y: -146..2, Z: -14..0+walls) with 6 PCB
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    file: case/out/bootsel_button.stl
    role: button
    process: mjf
    material: PA12
    finish: matte dark grey
    color: '#5a5852'
    description: Captive bottom-accessible push button actuator cap at world XY=(155.0, -18.0) aligned
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    file: case/out/top_shell.stl
    role: shell
    process: mjf
    material: PA12
    finish: matte warm-grey / beige
    color: '#e5dec9'
    description: Classic stepped beige upper bezel framing the 5-row 58-key well with raised rear ledge
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    file: case/out/keycaps.stl
    role: button
    process: mjf
    material: PA12
    finish: matte warm-beige sculpted keycaps
    color: '#cbc2b0'
    decor: case/out/keycaps_legends.stl
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
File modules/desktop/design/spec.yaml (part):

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      implement: pcb+case
      source: prompt
      confidence: high
      notes: "Direct service USB-C 2.0 OTG flashing receptacle J_BOOT wired straight to CM5 USB2_P/N (pins 105/103)"
    - id: F_BOOT_BTN
      name: Rear nRPIBOOT recovery button
      kind: button
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      implement: pcb+case
      source: prompt
      confidence: high
      notes: "Tactile pushbutton SW_BOOT pulling CM5 nRPIBOOT (pin 93) low at power-up for rpiboot eMMC flashing"
    - id: P_HDMI
      name: Rear HDMI video output port
      kind: port
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      implement: pcb+case
      source: prompt
      confidence: high
      notes: "Momentary power pushbutton SW_PWR wired to CM5 PWR_BUT (pin 92)"
    - id: F_RF_VENT
      name: Rear/top RF-transparent antenna vent window
      kind: window
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      key_parts: [TYPE-C-31-D-06, CH224A, AO3407A, SY8205FCC, TLV62569DBVR]
      reference: "WCH CH224 datasheet application circuit (CFG1 56 kOhm resistor strapping for 15 V PD), Silergy SY8205FCC 30V 5A synchronous buck application circuit, and TI TLV62569DBVR 3.3V 2A buck application circuit"
    - id: cm5_core
      purpose: "Raspberry Pi Compute Module 5 dual 100-pin mezzanine interface feeding all six +5v_(Input) pins (77,79,81,83,85,87), tying +3.3v_(Output) (pins 84,86) directly to GPIO_VREF (pin 78), and routing PWR_BUT (pin 92) to SW_PWR"
      key_parts: [DF40C-100DS-0.4V, PTS526SM15SMTR2LFS]
      reference: "Raspberry Pi Compute Module 5 IO Board rev 2 KiCad reference design (pip.raspberrypi.com)"
    - id: usb_boot_and_host
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    - ["J_KB.DN1", "U_CM5.USB3-0-D_N"]
    - ["J_MOUSE.DP1", "U_CM5.USB3-1-D_P"]
    - ["J_MOUSE.DN1", "U_CM5.USB3-1-D_N"]
    - ["U_BL.CTRL", "U_CM5.GPIO18"]
  high_speed:
    - name: mipi_dsi1
      board: main
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      file: case/out/rear_bucket.stl
      role: shell
      process: mjf
      material: PA12 nylon
      finish: matte textured warm beige
      color: "#e6e0d4"
      description: "Main rear/top/side/base bucket enclosure with top carrying handle recess, lower side cooling louvers, rear port cutouts, and internal PCB mounting bosses"
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      file: case/out/front_bezel.stl
      role: shell
      process: mjf
      material: PA12 nylon
      finish: matte textured warm beige
      color: "#e6e0d4"
      description: "1984-style sculpted front bezel with deep 4:3 screen recess, lower-right horizontal SD media slot recess, and lower-left chin overhang"
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      - {at_mm: [95.0, 5.0, 14.0]}
      - {at_mm: [95.0, -79.0, 164.0]}
      - {at_mm: [95.0, -156.0, 326.75]}
    note: "4-wire JST-PH LED backlight anode/cathode harness (BL_LED_A on pin 1, BL_FB on pin 2, GND on pins 3-4) from TPS61165 driver to LCD panel, with BL_PWM kept local to U_BL.CTRL on the carrier PCB"
  - id: front_io_cable
    kind: ffc
    a: {part: pcba, connector: J_FIO}
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    quantity: "15 V / 3 A PD input -> 5.0 V / 5.0 A buck"
  - id: R4
    text: "Direct service USB-C 2.0 OTG flashing port (P_BOOT) wired straight to CM5 USB2_P/N (pins 105/103) with nRPIBOOT button (pin 93) and USB_OTG_ID bootstrap"
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    quantity: "1x USB-C OTG flashing port + 1x nRPIBOOT button"
  - id: R5
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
